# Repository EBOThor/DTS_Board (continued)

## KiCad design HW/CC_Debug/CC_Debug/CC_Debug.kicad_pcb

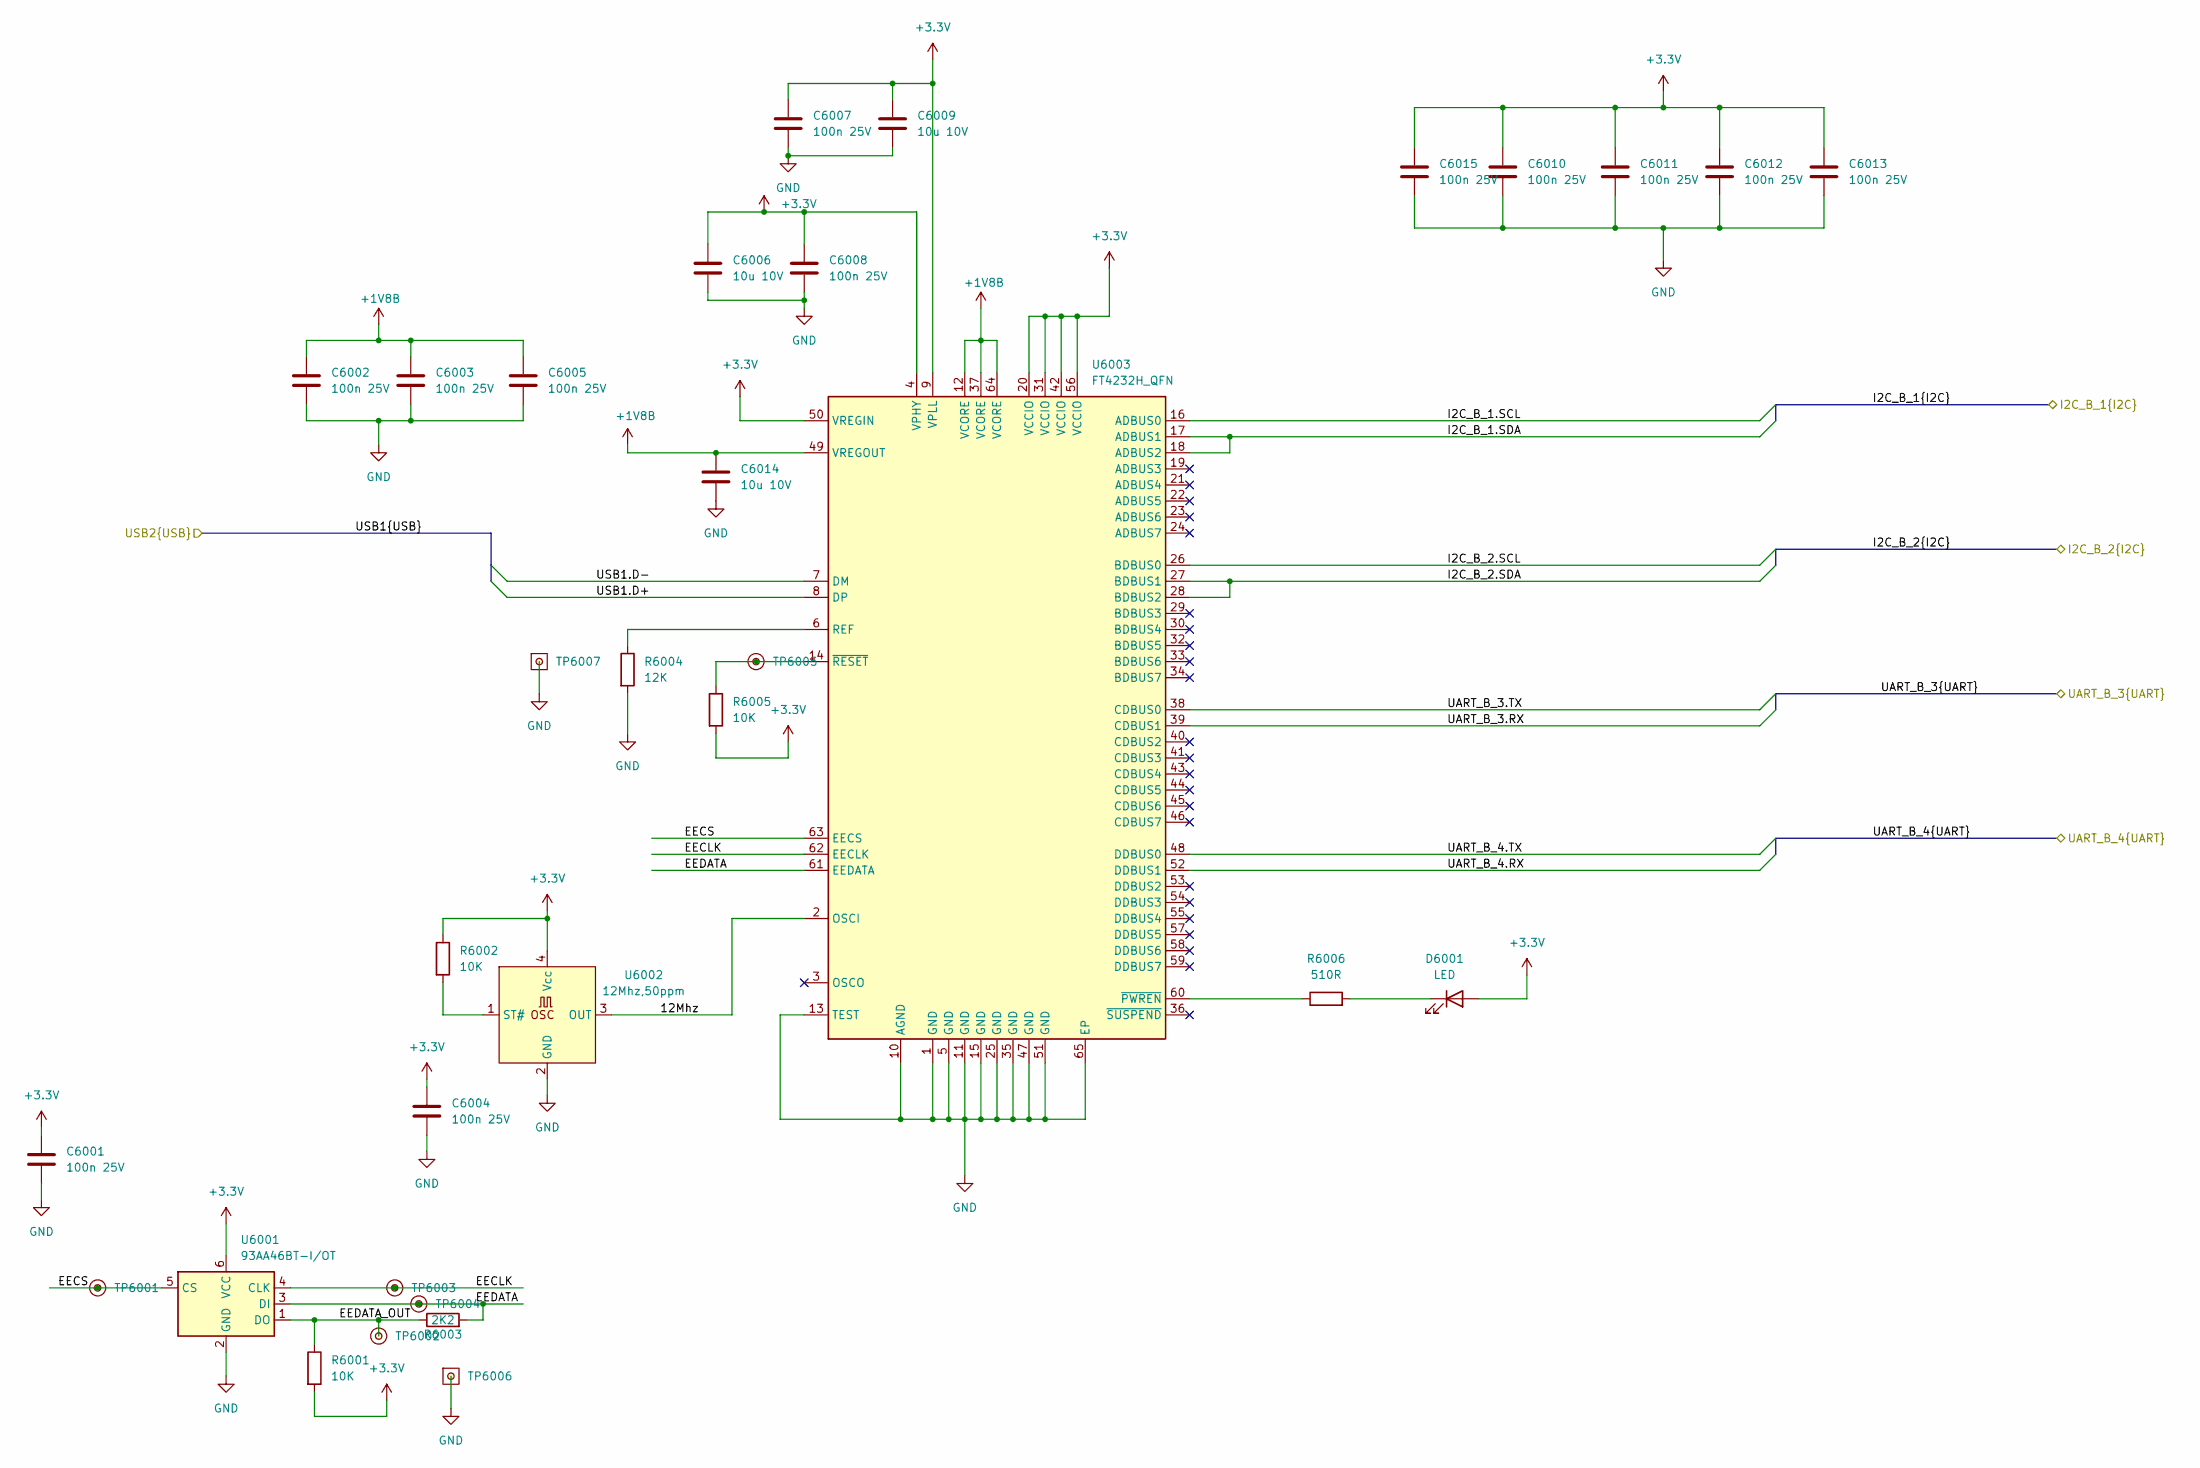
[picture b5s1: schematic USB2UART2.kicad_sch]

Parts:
C6001, C6002, C6003, C6004, C6005, C6007, C6008, C6010, C6011, C6012, C6013, C6015: 100n 25V; C_0603_1608Metric; MPN C;C;T1;S;P0603;NA
C6006, C6009, C6014: 10u 10V; C_0603_1608Metric; MPN C;C;T1;S;P0603;NA
D6001: LED; LED_0603_1608Metric
R6001, R6002, R6005: 10K; R_0603_1608Metric; MPN R;G;T1;S;P0603;NA
R6003: 2K2; R_0603_1608Metric; MPN R;G;T1;S;P0603;NA
R6004: 12K; R_0603_1608Metric; MPN R;G;T1;S;P0603;NA
R6006: 510R; R_0603_1608Metric; MPN R;G;T1;S;P0603;NA
TP6001, TP6002, TP6003, TP6004, TP6005: TestPoint; TestPoint_THTPad_D1.0mm_Drill0.5mm
TP6006, TP6007: TestPoint; TestPoint_THTPad_1.0x1.0mm_Drill0.5mm
U6001: 93AA46BT-I/OT; SOT-23-6; MPN 93AA46BT-I/OT
U6002: 12Mhz,50ppm; Oscillator_SMD_SeikoEpson_SG8002CE-4Pin_3.2x2.5mm; MPN SG3225CAN 12.0000M-TJGA6
U6003: FT4232H_QFN; QFN-64-1EP_9x9mm_P0.5mm_EP4.35x4.35mm; MPN FT4232HP

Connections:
+1V8B: C6002.1, C6003.1, C6005.1, C6014.1, U6003.12 (VCORE), U6003.37 (VCORE), U6003.49 (VREGOUT), U6003.64 (VCORE)
+3.3V: C6001.1, C6004.1, C6006.1, C6007.1, C6008.1, C6009.1, C6010.1, C6011.1, C6012.1, C6013.1, C6015.1, D6001.2 (A), R6001.2, R6002.1, R6005.2, U6001.6 (VCC), U6002.4 (Vcc), U6003.4 (VPHY), U6003.9 (VPLL), U6003.20 (VCCIO), U6003.31 (VCCIO), U6003.42 (VCCIO), U6003.50 (VREGIN), U6003.56 (VCCIO); also elsewhere on the board
/Isolation_output/I2C_B_1.SCL: U6003.16 (ADBUS0); also elsewhere on the board
/Isolation_output/I2C_B_1.SDA: U6003.17 (ADBUS1), U6003.18 (ADBUS2); also elsewhere on the board
/Isolation_output/I2C_B_2.SCL: U6003.26 (BDBUS0); also elsewhere on the board
/Isolation_output/I2C_B_2.SDA: U6003.27 (BDBUS1), U6003.28 (BDBUS2); also elsewhere on the board
/Isolation_output/UART_B_3.RX: U6003.39 (CDBUS1); also elsewhere on the board
/Isolation_output/UART_B_3.TX: U6003.38 (CDBUS0); also elsewhere on the board
/Isolation_output/UART_B_4.RX: U6003.52 (DDBUS1); also elsewhere on the board
/Isolation_output/UART_B_4.TX: U6003.48 (DDBUS0); also elsewhere on the board
/USB2.D+: U6003.8 (DP); also elsewhere on the board
/USB2.D-: U6003.7 (DM); also elsewhere on the board
/USB2UART2/12Mhz: U6002.3 (OUT), U6003.2 (OSCI)
/USB2UART2/EECLK: TP6003.1, U6001.4 (CLK), U6003.62 (EECLK)
/USB2UART2/EECS: TP6001.1, U6001.5 (CS), U6003.63 (EECS)
/USB2UART2/EEDATA: R6003.2, TP6004.1, U6001.3 (DI), U6003.61 (EEDATA)
/USB2UART2/EEDATA_OUT: R6001.1, R6003.1, TP6002.1, U6001.1 (DO)
GND: C6001.2, C6002.2, C6003.2, C6004.2, C6005.2, C6006.2, C6007.2, C6008.2, C6009.2, C6010.2, C6011.2, C6012.2, C6013.2, C6014.2, C6015.2, R6004.2, TP6006.1, TP6007.1, U6001.2 (GND), U6002.2 (GND), U6003.1 (GND), U6003.5 (GND), U6003.10 (AGND), U6003.11 (GND), U6003.13 (TEST), U6003.15 (GND), U6003.25 (GND), U6003.35 (GND), U6003.47 (GND), U6003.51 (GND), U6003.65 (EP); also elsewhere on the board
unnamed: D6001.1 (K), R6006.2
unnamed: R6002.2, U6002.1 (ST#)
unnamed: R6004.1, U6003.6 (REF)
unnamed: R6006.1, U6003.60 (~PWREN)
unnamed: R6005.1, TP6005.1, U6003.14 (~RESET)

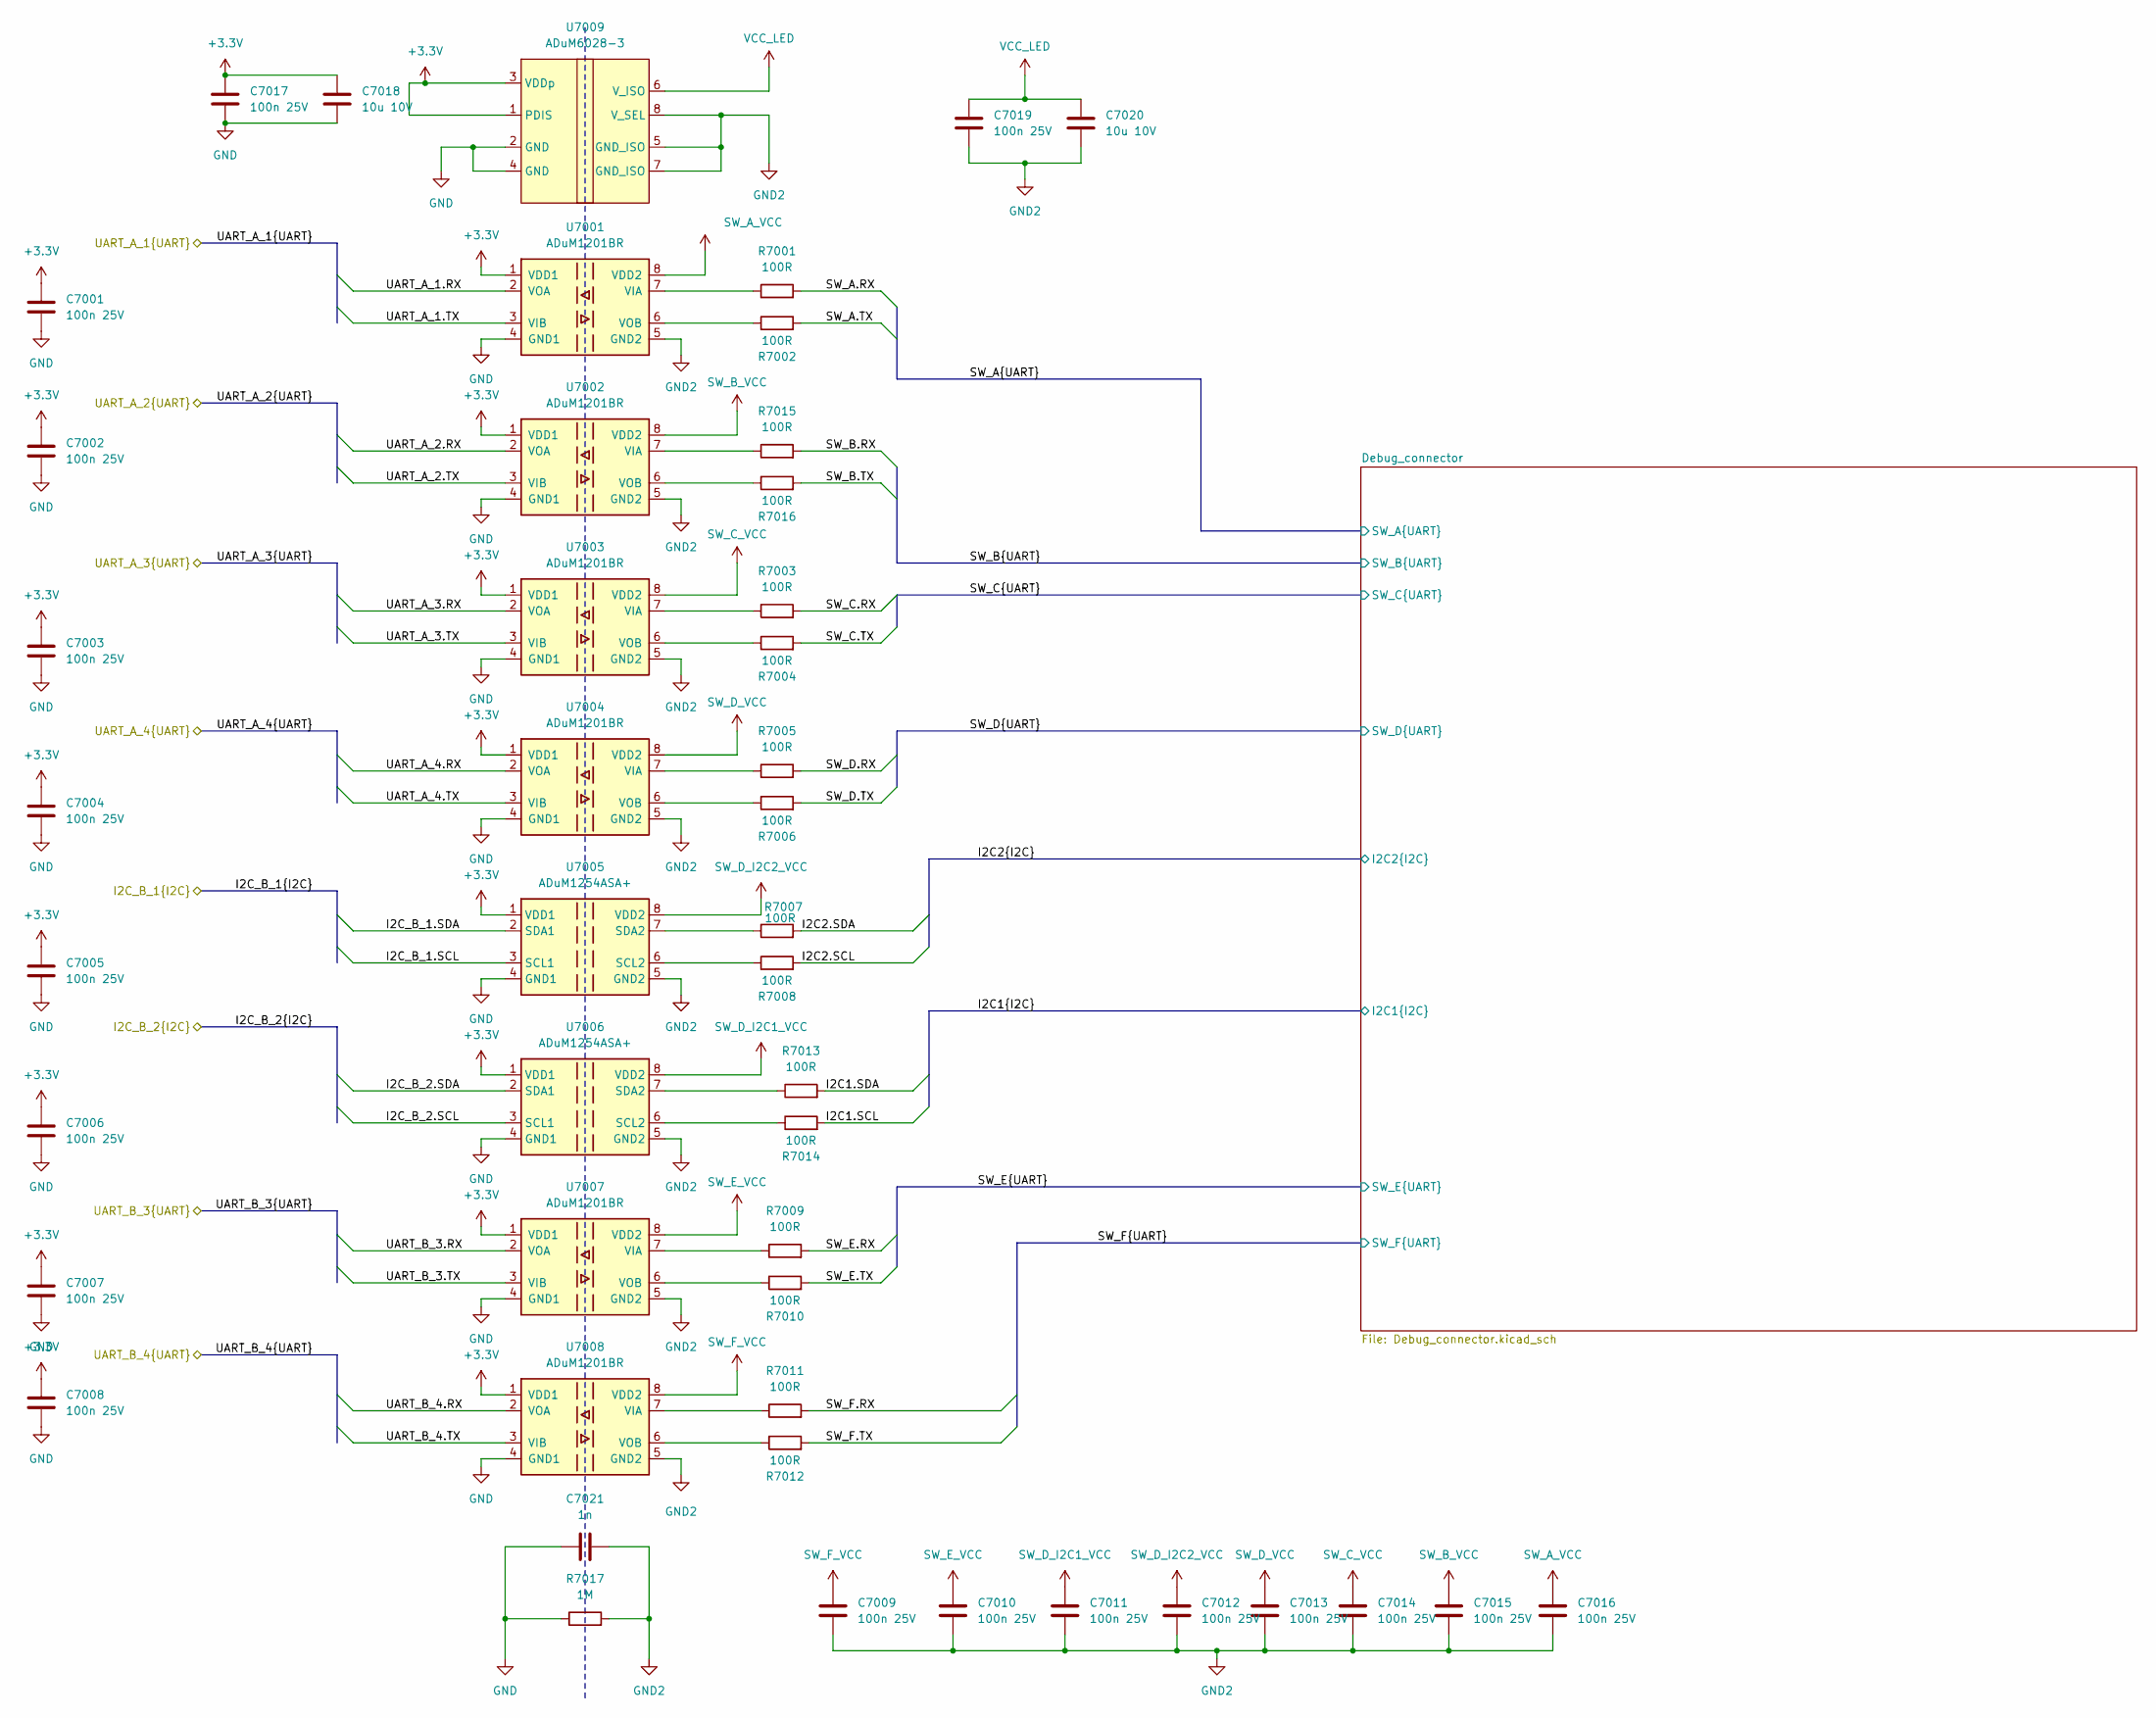
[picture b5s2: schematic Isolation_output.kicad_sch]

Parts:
C7001, C7002, C7003, C7004, C7005, C7006, C7007, C7008, C7009, C7010, C7011, C7012, C7013, C7014, C7015, C7016, C7017, C7019: 100n 25V; C_0603_1608Metric; MPN C;C;T1;S;P0603;NA
C7018, C7020: 10u 10V; C_0603_1608Metric; MPN C;C;T1;S;P0603;NA
C7021: 1n; C_1812_4532Metric
R7001, R7002, R7003, R7004, R7005, R7006, R7007, R7008, R7009, R7010, R7011, R7012, R7013, R7014, R7015, R7016: 100R; R_0603_1608Metric; MPN R;G;T1;S;P0603;NA
R7017: 1M; R_1210_3225Metric
U7001, U7002, U7003, U7004, U7007, U7008: ADuM1201BR; SOIC-8_3.9x4.9mm_P1.27mm; MPN ADuM1201BRZ
U7005, U7006: ADuM1254ASA+; SOIC-8_3.9x4.9mm_P1.27mm; MPN ADuM1254ASA+
U7009: ADuM6028-3; SOIC-8_7.5x5.85mm_P1.27mm; MPN ADuM6020-3

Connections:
+3.3V: C7001.1, C7002.1, C7003.1, C7004.1, C7005.1, C7006.1, C7007.1, C7008.1, C7017.1, C7018.1, U7001.1 (VDD1), U7002.1 (VDD1), U7003.1 (VDD1), U7004.1 (VDD1), U7005.1 (VDD1), U7006.1 (VDD1), U7007.1 (VDD1), U7008.1 (VDD1), U7009.1 (PDIS), U7009.3 (VDDp); also elsewhere on the board
/Isolation_output/I2C1.SCL: R7014.2; also elsewhere on the board
/Isolation_output/I2C1.SDA: R7013.2; also elsewhere on the board
/Isolation_output/I2C2.SCL: R7008.2; also elsewhere on the board
/Isolation_output/I2C2.SDA: R7007.2; also elsewhere on the board
/Isolation_output/I2C_B_1.SCL: U7005.3 (SCL1); also elsewhere on the board
/Isolation_output/I2C_B_1.SDA: U7005.2 (SDA1); also elsewhere on the board
/Isolation_output/I2C_B_2.SCL: U7006.3 (SCL1); also elsewhere on the board
/Isolation_output/I2C_B_2.SDA: U7006.2 (SDA1); also elsewhere on the board
/Isolation_output/SW_A.RX: R7001.2; also elsewhere on the board
/Isolation_output/SW_A.TX: R7002.2; also elsewhere on the board
/Isolation_output/SW_B.RX: R7015.2; also elsewhere on the board
/Isolation_output/SW_B.TX: R7016.2; also elsewhere on the board
/Isolation_output/SW_C.RX: R7003.2; also elsewhere on the board
/Isolation_output/SW_C.TX: R7004.2; also elsewhere on the board
/Isolation_output/SW_D.RX: R7005.2; also elsewhere on the board
/Isolation_output/SW_D.TX: R7006.2; also elsewhere on the board
/Isolation_output/SW_E.RX: R7009.2; also elsewhere on the board
/Isolation_output/SW_E.TX: R7010.2; also elsewhere on the board
/Isolation_output/SW_F.RX: R7011.2; also elsewhere on the board
/Isolation_output/SW_F.TX: R7012.2; also elsewhere on the board
/Isolation_output/UART_A_1.RX: U7001.2 (VOA); also elsewhere on the board
/Isolation_output/UART_A_1.TX: U7001.3 (VIB); also elsewhere on the board
/Isolation_output/UART_A_2.RX: U7002.2 (VOA); also elsewhere on the board
/Isolation_output/UART_A_2.TX: U7002.3 (VIB); also elsewhere on the board
/Isolation_output/UART_A_3.RX: U7003.2 (VOA); also elsewhere on the board
/Isolation_output/UART_A_3.TX: U7003.3 (VIB); also elsewhere on the board
/Isolation_output/UART_A_4.RX: U7004.2 (VOA); also elsewhere on the board
/Isolation_output/UART_A_4.TX: U7004.3 (VIB); also elsewhere on the board
/Isolation_output/UART_B_3.RX: U7007.2 (VOA); also elsewhere on the board
/Isolation_output/UART_B_3.TX: U7007.3 (VIB); also elsewhere on the board
/Isolation_output/UART_B_4.RX: U7008.2 (VOA); also elsewhere on the board
/Isolation_output/UART_B_4.TX: U7008.3 (VIB); also elsewhere on the board
GND: C7001.2, C7002.2, C7003.2, C7004.2, C7005.2, C7006.2, C7007.2, C7008.2, C7017.2, C7018.2, C7021.1, R7017.1, U7001.4 (GND1), U7002.4 (GND1), U7003.4 (GND1), U7004.4 (GND1), U7005.4 (GND1), U7006.4 (GND1), U7007.4 (GND1), U7008.4 (GND1), U7009.2 (GND), U7009.4 (GND); also elsewhere on the board
GND2: C7009.2, C7010.2, C7011.2, C7012.2, C7013.2, C7014.2, C7015.2, C7016.2, C7019.2, C7020.2, C7021.2, R7017.2, U7001.5 (GND2), U7002.5 (GND2), U7003.5 (GND2), U7004.5 (GND2), U7005.5 (GND2), U7006.5 (GND2), U7007.5 (GND2), U7008.5 (GND2), U7009.5 (GND_ISO), U7009.7 (GND_ISO), U7009.8 (V_SEL); also elsewhere on the board
unnamed: R7001.1, U7001.7 (VIA)
unnamed: R7002.1, U7001.6 (VOB)
unnamed: R7015.1, U7002.7 (VIA)
unnamed: R7016.1, U7002.6 (VOB)
unnamed: R7003.1, U7003.7 (VIA)
unnamed: R7004.1, U7003.6 (VOB)
unnamed: R7005.1, U7004.7 (VIA)
unnamed: R7006.1, U7004.6 (VOB)
unnamed: R7008.1, U7005.6 (SCL2)
unnamed: R7007.1, U7005.7 (SDA2)
unnamed: R7014.1, U7006.6 (SCL2)
unnamed: R7013.1, U7006.7 (SDA2)
unnamed: R7009.1, U7007.7 (VIA)
unnamed: R7010.1, U7007.6 (VOB)
unnamed: R7011.1, U7008.7 (VIA)
unnamed: R7012.1, U7008.6 (VOB)
SW_A_VCC: C7016.1, U7001.8 (VDD2); also elsewhere on the board
SW_B_VCC: C7015.1, U7002.8 (VDD2); also elsewhere on the board
SW_C_VCC: C7014.1, U7003.8 (VDD2); also elsewhere on the board
SW_D_I2C1_VCC: C7011.1, U7006.8 (VDD2); also elsewhere on the board
SW_D_I2C2_VCC: C7012.1, U7005.8 (VDD2); also elsewhere on the board
SW_D_VCC: C7013.1, U7004.8 (VDD2); also elsewhere on the board
SW_E_VCC: C7010.1, U7007.8 (VDD2); also elsewhere on the board
SW_F_VCC: C7009.1, U7008.8 (VDD2); also elsewhere on the board
VCC_LED: C7019.1, C7020.1, U7009.6 (V_ISO); also elsewhere on the board

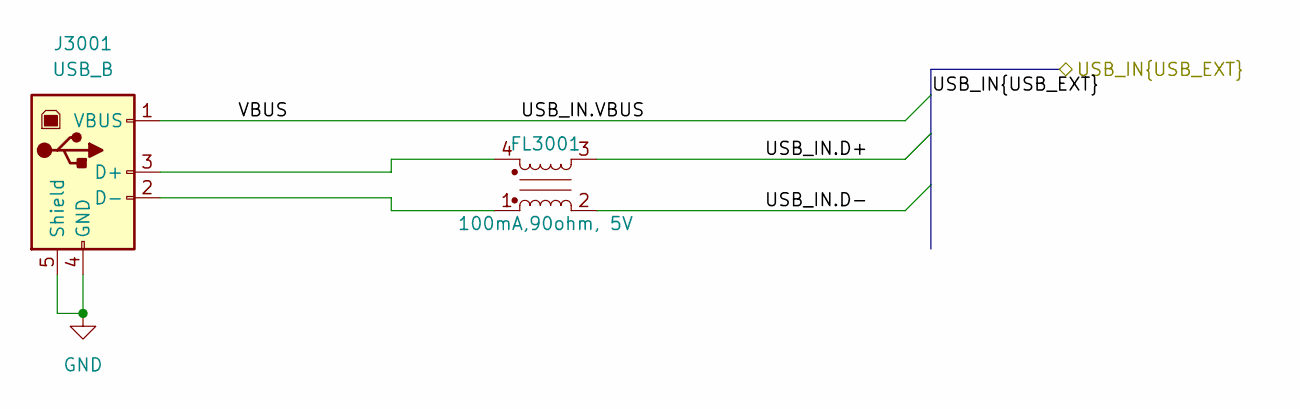
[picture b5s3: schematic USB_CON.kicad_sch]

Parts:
FL3001: 100mA,90ohm, 5V; DLM0NSM900HY2D; MPN DLM0NSM900HY2D
J3001: USB_B; USB_B_TE_5787834_Vertical

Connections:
/USB.D+: FL3001.3; also elsewhere on the board
/USB.D-: FL3001.2; also elsewhere on the board
/USB.VBUS: J3001.1 (VBUS); also elsewhere on the board
GND: J3001.4 (GND), J3001.5 (Shield); also elsewhere on the board
unnamed: FL3001.4, J3001.3 (D+)
unnamed: FL3001.1, J3001.2 (D-)

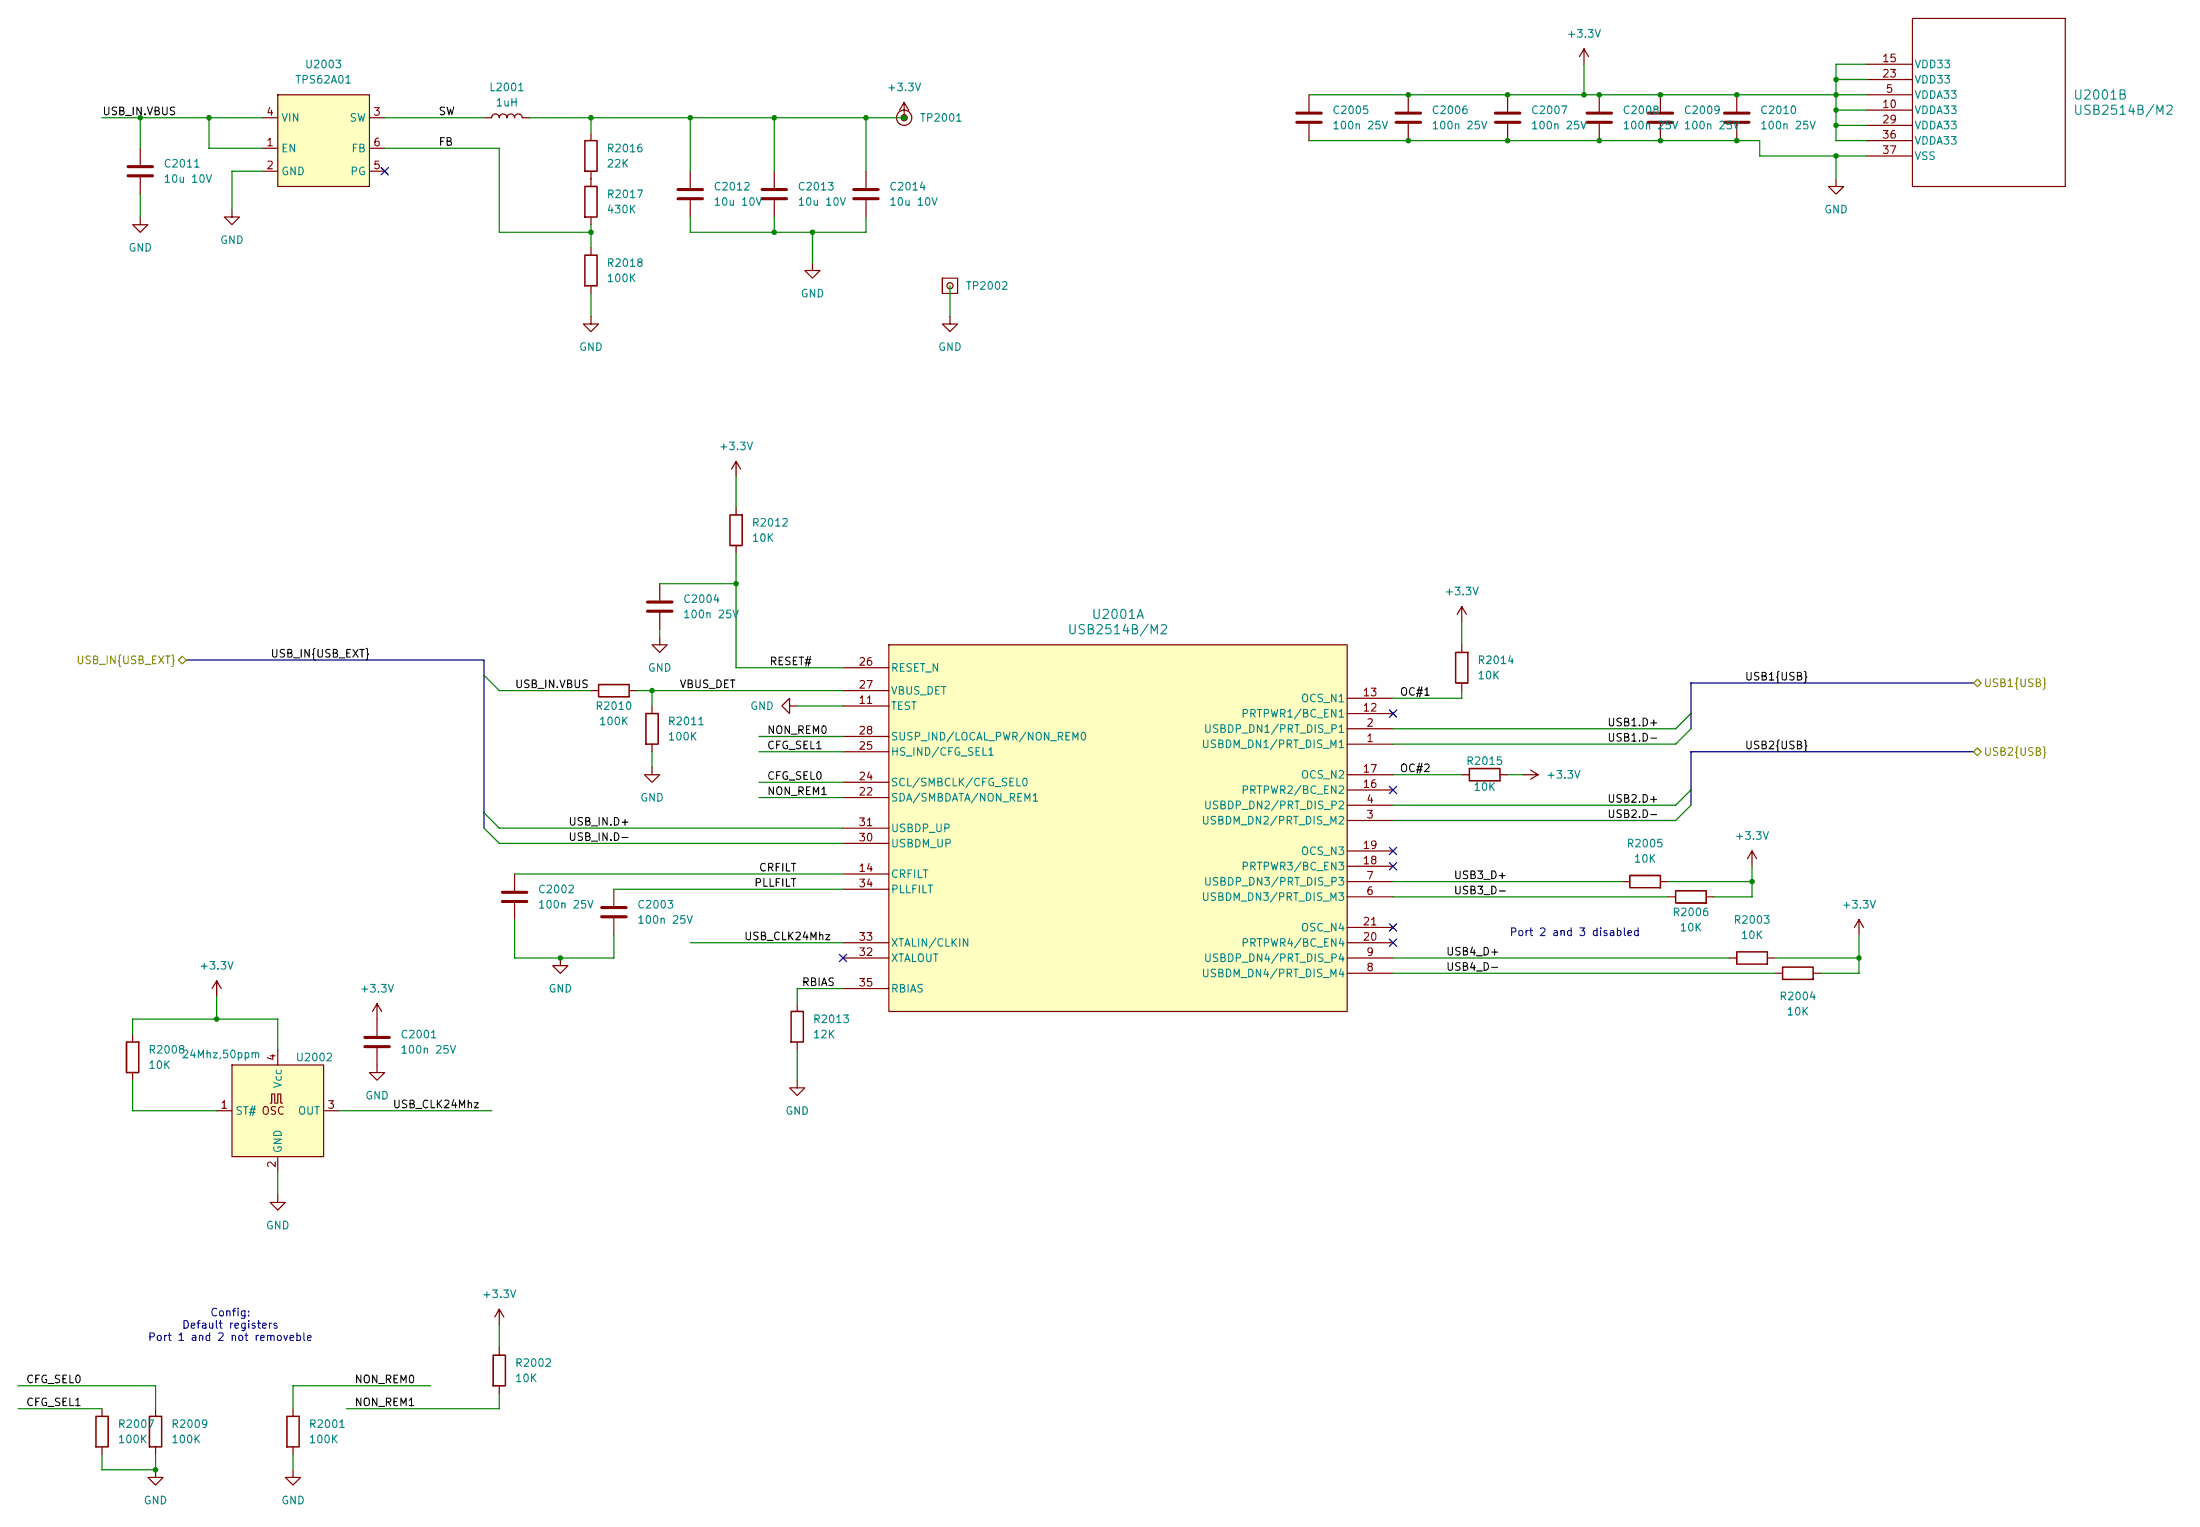
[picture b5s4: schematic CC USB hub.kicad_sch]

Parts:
C2001, C2002, C2003, C2004, C2005, C2006, C2007, C2008, C2009, C2010: 100n 25V; C_0603_1608Metric; MPN C;C;T1;S;P0603;NA
C2011, C2012, C2013, C2014: 10u 10V; C_0603_1608Metric; MPN C;C;T1;S;P0603;NA
L2001: 1uH; L_0805_2012Metric; MPN CIGT201208EH1R0MNE
R2001, R2007, R2009, R2010, R2011, R2018: 100K; R_0603_1608Metric; MPN R;G;T1;S;P0603;NA
R2002, R2003, R2004, R2005, R2006, R2008, R2012, R2014, R2015: 10K; R_0603_1608Metric; MPN R;G;T1;S;P0603;NA
R2013: 12K; R_0603_1608Metric; MPN R;G;T1;S;P0603;NA
R2016: 22K; R_0603_1608Metric; MPN R;G;T1;S;P0603;NA
R2017: 430K; R_0603_1608Metric; MPN R;G;T1;S;P0603;NA
TP2001: TestPoint; TestPoint_THTPad_D1.0mm_Drill0.5mm
TP2002: TestPoint; TestPoint_THTPad_1.0x1.0mm_Drill0.5mm
U2001: USB2514B/M2; SQFN36_6X6_MCH; MPN USB2514B
U2002: 24Mhz,50ppm; Oscillator_SMD_SeikoEpson_SG8002CE-4Pin_3.2x2.5mm; MPN SG3225CAN 24.0000M-TJGA6
U2003: TPS62A01; SOT-23-6; MPN TPS62A01

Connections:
+3.3V: C2001.1, C2005.1, C2006.1, C2007.1, C2008.1, C2009.1, C2010.1, C2012.1, C2013.1, C2014.1, L2001.2, R2002.1, R2003.2, R2004.2, R2005.2, R2006.2, R2008.2, R2012.2, R2014.2, R2015.2, R2016.1, TP2001.1, U2001.5 (VDDA33), U2001.10 (VDDA33), U2001.15 (VDD33), U2001.23 (VDD33), U2001.29 (VDDA33), U2001.36 (VDDA33), U2002.4 (Vcc); also elsewhere on the board
/USB1.D+: U2001.2 (USBDP_DN1/PRT_DIS_P1); also elsewhere on the board
/USB1.D-: U2001.1 (USBDM_DN1/PRT_DIS_M1); also elsewhere on the board
/USB2.D+: U2001.4 (USBDP_DN2/PRT_DIS_P2); also elsewhere on the board
/USB2.D-: U2001.3 (USBDM_DN2/PRT_DIS_M2); also elsewhere on the board
/USB hub/CFG_SEL0: R2009.1, U2001.24 (SCL/SMBCLK/CFG_SEL0)
/USB hub/CFG_SEL1: R2007.1, U2001.25 (HS_IND/CFG_SEL1)
/USB hub/CRFILT: C2002.1, U2001.14 (CRFILT)
/USB hub/FB: R2017.2, R2018.1, U2003.6 (FB)
/USB hub/NON_REM0: R2001.1, U2001.28 (SUSP_IND/LOCAL_PWR/NON_REM0)
/USB hub/NON_REM1: R2002.2, U2001.22 (SDA/SMBDATA/NON_REM1)
/USB hub/OC#1: R2014.1, U2001.13 (OCS_N1)
/USB hub/OC#2: R2015.1, U2001.17 (OCS_N2)
/USB hub/PLLFILT: C2003.1, U2001.34 (PLLFILT)
/USB hub/RBIAS: R2013.1, U2001.35 (RBIAS)
/USB hub/RESET#: C2004.1, R2012.1, U2001.26 (RESET_N)
/USB hub/SW: L2001.1, U2003.3 (SW)
/USB hub/USB3_D+: R2005.1, U2001.7 (USBDP_DN3/PRT_DIS_P3)
/USB hub/USB3_D-: R2006.1, U2001.6 (USBDM_DN3/PRT_DIS_M3)
/USB hub/USB4_D+: R2003.1, U2001.9 (USBDP_DN4/PRT_DIS_P4)
/USB hub/USB4_D-: R2004.1, U2001.8 (USBDM_DN4/PRT_DIS_M4)
/USB hub/USB_CLK24Mhz: U2001.33 (XTALIN/CLKIN), U2002.3 (OUT)
/USB hub/VBUS_DET: R2010.2, R2011.1, U2001.27 (VBUS_DET)
/USB.D+: U2001.31 (USBDP_UP); also elsewhere on the board
/USB.D-: U2001.30 (USBDM_UP); also elsewhere on the board
/USB.VBUS: C2011.1, R2010.1, U2003.1 (EN), U2003.4 (VIN); also elsewhere on the board
GND: C2001.2, C2002.2, C2003.2, C2004.2, C2005.2, C2006.2, C2007.2, C2008.2, C2009.2, C2010.2, C2011.2, C2012.2, C2013.2, C2014.2, R2001.2, R2007.2, R2009.2, R2011.2, R2013.2, R2018.2, TP2002.1, U2001.11 (TEST), U2001.37 (VSS), U2002.2 (GND), U2003.2 (GND); also elsewhere on the board
unnamed: R2016.2, R2017.1
unnamed: R2008.1, U2002.1 (ST#)

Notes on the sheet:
Port 2 and 3 disabled
Config: Default registers Port 1 and 2 not removeble

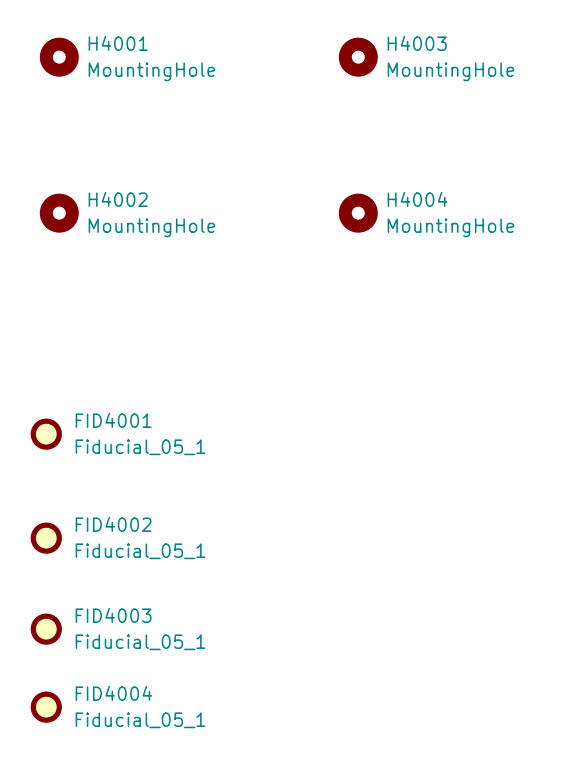
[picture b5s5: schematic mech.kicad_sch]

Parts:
FID4001, FID4002, FID4003, FID4004: Fiducial_05_1; Fiducial_0.5mm_Mask1mm
H4001, H4002, H4003, H4004: MountingHole; MountingHole_3.2mm_M3
